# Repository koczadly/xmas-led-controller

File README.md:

# Alrite?

## Introduction
This repository contains files from a personal project. The aim was to create a small microcontroller-driven LED module to replace a broken incandescent-based fibre optic Christmas tree. This is my first project involving PIC microcontrollers, and the second PCB I've designed; mistakes and questionable design techniques are to be expected.

### Files
- PCB files are in [`hardware`](/hardware/) (KiCad project)
- Software code is in [`firmware`](/firmware/) (MPLAB X project)

Feel free to re-use or modify this project to fit your needs, or use as a reference for PCB design or PIC software development.

## Finished product
A range of final images can be found in the [`media` folder](/media/).

## Bill of materials
MPN | Type | Quantity | Unit cost (GBP) | Purpose
--- | --- | --- | --- | ---
[**PIC12F683**](https://www.microchip.com/wwwproducts/en/PIC12F683) (DIP) | Microcontroller | 1 | £0.45 | Controls visual animations and user input
[**74HC595**](http://www.ti.com/lit/ds/symlink/sn74hc595.pdf) (DIP) | 8-bit Shift Register | 1 | £0.05 | Controls outputs to outer blue LEDs from the MCU
N/A | 3mm Blue LED | 8 | £0.01 | Outer LED ring
N/A | 5mm Green LED | 3 | £0.01 | Inner LEDs (PWM-driven)
N/A | 5mm White LED | 1 | £0.01 | Inner strobing LED
[**2N3904**](https://www.onsemi.com/pub/Collateral/2N3903-D.PDF) (TO-92) | NPN Transistor | 10 | £0.01 | Drives each individual controllable LED group (8x Blue, 1x Green, 1x White)
[N/A](https://www.ebay.co.uk/itm/AC-1-5A-250V-3A-125V-Red-Square-Momentary-SPST-Push-Button-Switch-6-Pcs/183740567110) | SPST Momentary Switch | 1 | £0.30 | User input for changing displayed animation/colour
N/A | 1000μF (25V) Electrolytic Capacitor | 1 | £0.10 | Supply voltage smoothing
N/A | 100nF (50V) Ceramic Capacitor | 1 | £0.01 | Decoupling capacitor for MCU
N/A | 10k Resistor (1/4W) | 1 | £0.001 | Input switch pull-down resistor
N/A | 1k Resistor (1/4W) | 10 | £0.001 | Transistor base current limiters
N/A | 150R Resistor (1/4W) | 8 | £0.001 | Current limiter for blue LEDs
N/A | 120R Resistor (1/4W) | 3 | £0.001 | Current limiter for green LEDs
N/A | 62R Resistor (1/4W) | 1 | £0.001 | Current limiter for white LED

<br>

**Total component cost: £1.15**  
**PCB panel cost (DIY): £0.35**  
**Total cost: £1.50** *(Not including etchant, solder or original tree product)*  

---

## Design notes & constraints
There were various constraints throughout this project, the most difficult one being that I could only produce a single-sided PCB, making overlaps impossible without using space for a 0Ω link. The size of the board was also restricted to *68mm x 92mm*, otherwise the module wouldn't fit into the tree's current plastic base housing. Drill holes also had to be made and inserted at defined locations so the board could easily be screwed into the unit using pre-existing screw mounts from the previous incandescent arrangement.

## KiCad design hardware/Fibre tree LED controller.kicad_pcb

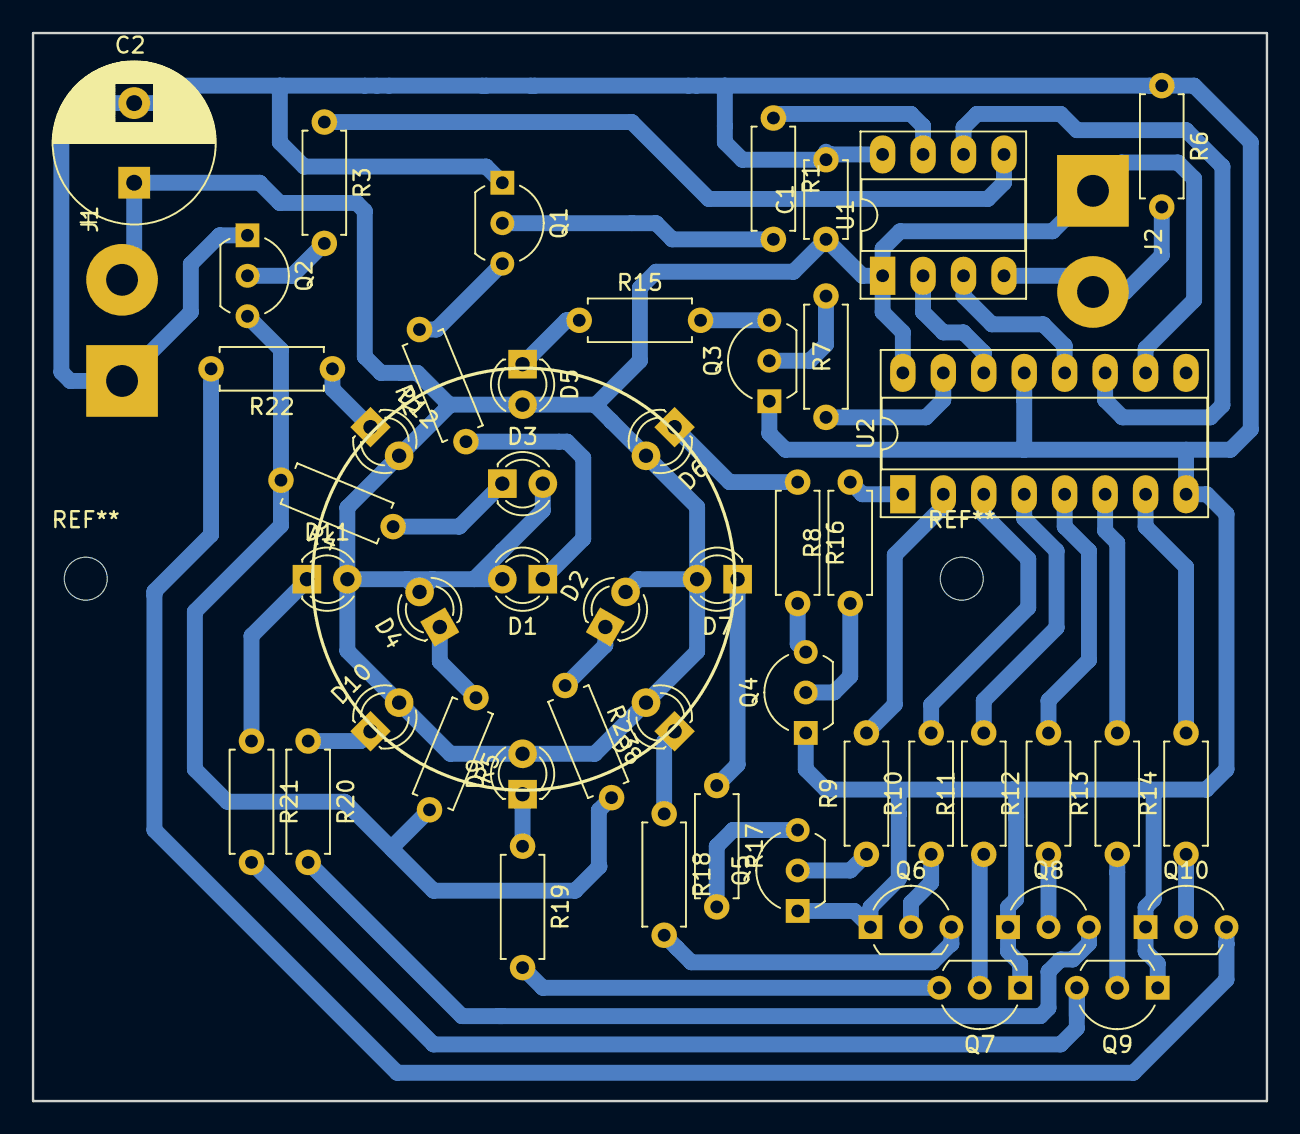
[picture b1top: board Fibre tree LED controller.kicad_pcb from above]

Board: 2 copper layers, 77.5 x 67.1 mm, 51 parts (0 on the bottom side), 48 nets.

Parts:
C1: 10nf; C_Disc_D4.7mm_W2.5mm_P5.00mm
C2: 1000uf; CP_Radial_D10.0mm_P5.00mm
D1: LED-W; LED_D3.0mm_FlatTop
D2, D3, D4: LED-G; LED_D3.0mm_FlatTop
D5, D6, D7, D8, D9, D10, D11, D12: LED-B; LED_D3.0mm_FlatTop
J1, J2: Conn_01x02; SolderWirePad_1x02_P7.62mm_Drill2mm
Q1, Q2, Q3, Q4, Q5, Q6, Q7, Q8, Q9, Q10: 2N3904; TO-92L_Inline_Wide
R1, R3, R7, R8, R9, R10, R11, R12, R13, R14: 1k; R_Axial_DIN0207_L6.3mm_D2.5mm_P7.62mm_Horizontal
R2: 62; R_Axial_DIN0207_L6.3mm_D2.5mm_P7.62mm_Horizontal
R4, R5, R23: 120; R_Axial_DIN0207_L6.3mm_D2.5mm_P7.62mm_Horizontal
R6: 10k; R_Axial_DIN0207_L6.3mm_D2.5mm_P7.62mm_Horizontal
R15, R16, R17, R18, R19, R20, R21, R22: 150; R_Axial_DIN0207_L6.3mm_D2.5mm_P7.62mm_Horizontal
U1: PIC12F683-IP; DIP-8_W7.62mm_Socket_LongPads
U2: 74HC595; DIP-16_W7.62mm_Socket_LongPads

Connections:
+5V: C1.1, C2.1, D1.2, D2.2, D3.2, D4.2, D5.2, D6.2, D7.2, D8.2, D9.2, D10.2, D11.2, D12.2, J1.2, J2.1, U1.1, U2.10, U2.16
GND: C1.2, C2.2, J1.1, Q1.1, Q2.1, Q3.1, Q4.1, Q5.1, Q6.1, Q7.1, Q8.1, Q9.1, Q10.1, R6.1, U1.8, U2.8, U2.13
unnamed: D1.1, R2.1
unnamed: D2.1, R23.1
unnamed: D3.1, R4.1
unnamed: D4.1, R5.1
unnamed: D5.1, R15.1
unnamed: D6.1, R16.1
unnamed: D7.1, R17.1
unnamed: D8.1, R18.1
unnamed: D9.1, R19.1
unnamed: D10.1, R20.1
unnamed: D11.1, R21.1
unnamed: D12.1, R22.1
unnamed: J2.2, R6.2, U1.4
unnamed: Q1.2, R1.2
unnamed: Q1.3, R2.2
unnamed: Q2.2, R3.2
unnamed: Q2.3, R4.2, R5.2, R23.2
unnamed: Q3.2, R7.1
unnamed: Q3.3, R15.2
unnamed: Q4.2, R8.1
unnamed: Q4.3, R16.2
unnamed: Q5.2, R9.1
unnamed: Q5.3, R17.2
unnamed: Q6.2, R10.1
unnamed: Q6.3, R18.2
unnamed: Q7.2, R11.1
unnamed: Q7.3, R19.2
unnamed: Q8.2, R12.1
unnamed: Q8.3, R20.2
unnamed: Q9.2, R13.1
unnamed: Q9.3, R21.2
unnamed: Q10.2, R14.1
unnamed: Q10.3, R22.2
unnamed: R1.1, U1.7
unnamed: R3.1, U1.5
unnamed: R7.2, U2.15
unnamed: R8.2, U2.1
unnamed: R9.2, U2.2
unnamed: R10.2, U2.3
unnamed: R11.2, U2.4
unnamed: R12.2, U2.5
unnamed: R13.2, U2.6
unnamed: R14.2, U2.7
unnamed: U1.2, U2.14
unnamed: U1.3, U2.12
unnamed: U1.6, U2.11

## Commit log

2019-01-15 Add PIC software source code
2019-01-15 Add hardware (PCB & schem) files
2019-01-15 Add final compile/render files
2019-01-15 Add readme file
2019-01-15 Remove /nbproject/ from ignored directories in software
2019-01-15 Update readme doc
2019-06-19 Add demo images
2019-06-19 Resize images
2019-06-19 Add note to readme
2019-06-19 Add new images and documentation
2019-07-02 Reorganise and add documentation
2019-07-02 Rename files
2019-07-02 Fix documentation
2019-11-18 Generate BOM
2019-11-18 Update README to include BOM
2019-11-18 Fix README formatting
2019-11-18 Add specifics to README BOM
2020-04-11 Add new renders to /demo/
2020-06-24 Update README, correct component prices and descriptions.
2021-06-27 Move docs and notes to /documentation/ folder
2025-05-03 Create LICENSE
2025-05-03 Add better images, update README
2025-05-03 Add missing photo
